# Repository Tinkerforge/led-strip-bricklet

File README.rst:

LED Strip Bricklet
==================

This repository contains the firmware source code and the hardware design
files. The documentation generator configs can be found at
https://github.com/Tinkerforge/generators

Repository Content
------------------

software/:
 * examples/: Examples for all supported languages
 * build/: Compiled files
 * src/: Source code of firmware
 * Makefile: Makefile to build project

hardware/:
 * Contains KiCad project files and additionally schematics as PDF

datasheets/:
 * Contains datasheets for sensors and complex ICs that are used

Hardware
--------

The hardware is designed with the open source EDA Suite KiCad
(http://www.kicad.org). Before you are able to open the files,
you have to install the Tinkerforge kicad-libraries
(https://github.com/Tinkerforge/kicad-libraries). You can either clone
them directly in hardware/ or clone them in a separate folder and
symlink them into hardware/
(ln -s kicad_path/kicad-libraries project_path/hardware). After that you
can open the .pro file in hardware/ with KiCad and from there view and
modify the schematics and the PCB layout.

Software
--------

If you want to do your own Brick/Bricklet firmware development we highly
recommend that you use our build environment setup script and read the
tutorial (https://www.tinkerforge.com/en/doc/Tutorials/Tutorial_Build_Environment/Tutorial.html).

To compile the C code we recommend you to install the newest GNU Arm Embedded
Toolchain (https://launchpad.net/gcc-arm-embedded/+download).
You also need to install bricklib (https://github.com/Tinkerforge/bricklib)
and brickletlib (https://github.com/Tinkerforge/brickletlib).

You can either clone it directly in software/src/ or clone it in a
separate folder and symlink it into software/src/
(ln -s bricklib_path/bricklib project_path/software/src/ and
ln -s brickletlib_path/brickletlib project_path/software/src/).
Finally make sure to have CMake installed
(http://www.cmake.org/cmake/resources/software.html).

After that you can build the firmware by invoking make in software/.
The firmware (.bin) can then be found in software/build/ and uploaded
with brickv (click button "Flashing" on start screen).

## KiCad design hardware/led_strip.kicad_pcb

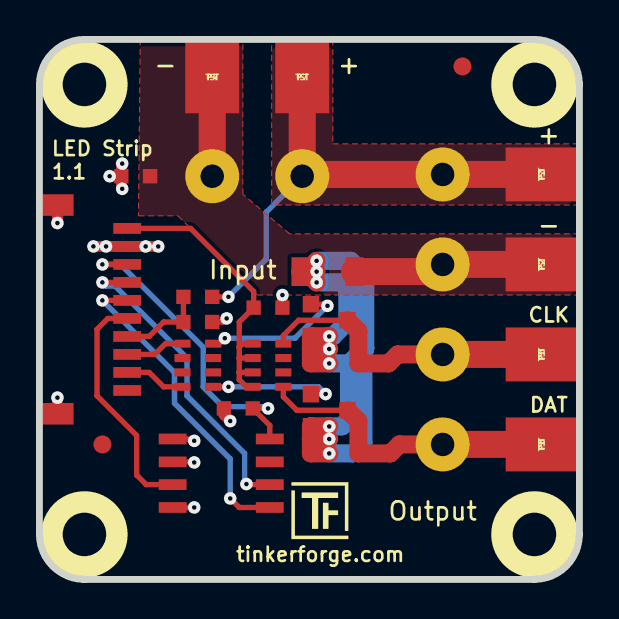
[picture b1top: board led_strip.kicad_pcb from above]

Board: 2 copper layers, 30.0 x 30.0 mm, 31 parts (0 on the bottom side), 16 nets.

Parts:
C1, C2: 100nF; C0603
D1, D2: ESD5V0D3B-TP; SOD-323
F1: FUSE; F1206
Fiducial_Mark: VAL**; Fiducial_Mark
Fiducial_Mark#2: VAL**; Fiducial_Mark
J1, J2, J3: AKL_5_2
L1: FB; C0603
P1: CON-SENSOR
P2, P3, P4, P5, P6, P7: TST; SOLDER_PAD2
Q1, Q2: 2N7002P; SOT23GDS
R1: 1k; R0603
R2: 10k; R0603
RP1: 470; 4X0603
RP2: 1k; 4X0603
U1: M24C64; SOIC8
U2, U3, U4, U5: DRILL; DRILL_NP
VAL: WEEE_7mm
VAL#2: CE_5mm

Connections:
+5V: C2.1, P1.1, RP2.5, RP2.6, RP2.7, RP2.8
AGND: F1.2, J1.1, J2.2, L1.2, P2.1, P4.1
GND: C1.2, C2.2, L1.1, P1.2, P1.EP, R1.1, U1.1, U1.2, U1.4
unnamed: D1.1, J3.1, P5.1, Q1.D, RP2.1
unnamed: D1.2, D2.2, F1.1, Q1.S, Q2.S
unnamed: D2.1, J3.2, P6.1, Q2.D, RP2.4
unnamed: J1.2, J2.1, P3.1, P7.1, R2.2
unnamed: P1.4, U1.6
unnamed: P1.5, U1.5
unnamed: P1.6, U1.3
unnamed: P1.7, R1.2, R2.1
unnamed: P1.8, RP1.8
unnamed: P1.9, RP1.5
unnamed: Q1.G, RP1.1
unnamed: Q2.G, RP1.4
VCC: C1.1, P1.3, U1.8

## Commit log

2013-09-17 Change optimization from 3 to 2
2013-09-17 Add support for multiple brick contexts
2013-09-20 c: Avoid unused parameter warning
2013-10-15 add hardware files
2013-10-17 add missing license file
2013-10-18 Fix name to fit naming standard
2013-10-29 Fix variable type in loop (we need uint16 instead of uint8)
2013-10-30 Add missing LED Strip examples for ruby and python
2013-10-30 Don't use data in case of error
2013-11-19 update schematic to correct resistor values
2013-11-19 update hardware files with new resistor values
2013-11-27 ruby: Fix whitespace
2013-12-02 Fix typo
2013-12-06 Add Get/SetClockFrequency function
2013-12-19 php: Cleanup example
2014-01-08 Fix typos
2014-01-10 Add Perl examples
2014-01-14 perl: Fix warning about unsharing the $led_strip variable
2014-02-07 Add Mathematica examples
2014-02-10 Perl Example Modified: LED Strip Bricklet callback
2014-02-10 perl: fixed namespace
2014-02-12 javascript: add examples
2014-02-18 javascript: examples fixed
2014-02-20 javascript: add html examples
2014-02-24 javascript: port 4280, startExample()
2014-02-28 javascript: Break long lines and cleanup whitespace
2014-03-05 Add LabVIEW examples
2014-03-06 labview: Add examples in LV2010 format
2014-03-31 matlab: add examples
2014-04-02 java: Unify constants style
2014-04-02 perl: Unify print style
2014-04-17 matlab: Adapt examples to new callback style
2014-04-17 matlab: Add parentheses to make pygments happy
2014-07-03 Add support for WS2811 and WS2812
2014-07-04 Make WS2811 and WS2812 protocol implementation more precise
2014-07-07 Update changelog
2014-07-10 Use timings based on measured values, not according to datasheet
2014-07-15 java: Replace System.console() usage with an Eclipse compatible pattern
2014-07-22 * Frame duration of 0 now means that no more frames shall be set * Set RGB values at least two times to make sure that they are really written * Fix possible overflow if Brick with two Bricklet conne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
2014-07-22 Add changelog for 2.0.5
2014-08-05 delphi: Remove unused variable
2014-12-02 Use ReadLine instead of ReadKey for C# example
2015-02-13 vbnet: Use ReadLine instead of ReadKey
    Because ReadKey doesn't work with a pipe as stdin on the RED Brick.
2015-03-02 windows: Stop cmake from searching for mingw32-make.exe
    Using MinGW Makefiles as generator makes cmake search for mingw32-make.exe
    which might not be installed because GnuWin32's make.exe is used instead.
2015-03-03 delphi: Fix type mismatch error in Delphi IDE
    Object Pascal doesn't allow static array definitions in function and
    procedure signatures. As workaround a external type definition has to
    be used.
    The Delphi IDE reports a type mismatch error if array [0..15] of byte
    and TArray0To15OfUInt8 are mixed. In contrast FPC allows to mix this.
2015-04-09 c: Whitespace
2015-07-08 new prototype of led strip bricklet
2015-07-25 Make JavaScript browser example textarea readonly
2015-07-27 Cleanup C/C++, C#, Java, Python and Ruby examples
2015-07-27 Simplify variable names in examples again
2015-07-28 Add missing final modifier in Java example and fix variable name in C/C++ example
2015-07-29 Reformat changelog
2015-08-07 Use full device class name in Python examples
2015-08-12 Fix minor warnings in C/C++ examples
2015-08-17 Cleanup Delphi examples
2015-08-18 Cleanup VB.NET examples
2015-08-19 Cleanup Perl examples
2015-09-09 Duplicate cmake call to fix bug during cmake creation
2015-09-25 drc run
2015-10-05 Generator based example cleanup
2015-11-12 matlab: Fix callback handling for R2014a
    http://undocumentedmatlab.com/blog/matlab-callbacks-for-java-events-in-r2014a
2015-11-25 Include date and commit into changelog
2016-05-18 c: Add missing device destroy call
2016-07-01 Make the change UID comment more explicit
2016-07-19 Add RGBW support for WS2812 style timing
2016-07-27 Add support for new chip type: LPD8806
2016-07-28 Add support for new chip type: APA102 (Adafruit DotStar)
2016-08-01 Add brightness control for APA102
    Does not work with Master Brick FW 2.4.0
2016-08-01 Use option functions to make code more readable
2016-08-01 Use Os
2016-08-01 Add datasheets for all supported chip types
2016-08-02 little cleanup
2016-08-11 Add channel mapping and code optimization
2016-08-11 Remove debug code
2016-09-01 Reduce code size by refactoring common and unused code
    Also free up a byte in the BrickContext.
2016-09-01 Cleanup bb_write functions
2016-09-01 Whitespace
2016-09-01 Add defines for channel mappings
2016-09-01 Add SK6812 datasheets
2016-09-02 Apply channel mapping in RGB(W) getter
    Restructure buffer handling to reduce code size.
    Alos fix frame_max_length calculation in RGBW mode.
2016-09-02 Add missing APA102 endframe
2016-09-02 Minor style cleanup
2016-09-02 Fix default channel mapping
2016-09-02 Fix loop in RGB(W) getters
2016-09-02 Send correct number of zero bytes for LPD8806
2016-09-06 Make channel mapping constants contain the actual mapping table
    Also store channels unmapped and map them before sending to the LEDs.
    This allows to change the mapping for already set RGB(W) values.
2016-09-06 Add option to disable frame-rendered callback
2016-09-06 Add missing setter return
2016-09-07 Fix green flash after reset
    MOSFET inverts logic, initial pin state needs to be high to ensure low
    output until first frame.
2016-09-07 Use local bc variable
2016-09-08 Add changelog commit after the fact
2017-04-13 csharp: Adapt example
2017-06-02 octave: Use javaObject instead of deprecated java_new
2017-07-31 Fix broken symbols
2017-07-31 New schematic version
2017-07-31 Add 3d information (final)
2017-07-31 Add 3d model (*.step & *.FCStd)
2017-11-30 Update examples from generator
2017-12-07 mathematica: Also generate .nb files
2018-02-19 javascript: Close div tag correctly
2018-02-20 Cleanup KiCad libraries config
    Ensure LibDir=kicad-libraries and LibName1=tinkerforge.
    Remove special library.
2018-03-28 specify fuse
2018-05-11 Rename files
2018-05-24 perl: Use strict in examples
2018-07-11 Add Makefile with docker support
2018-07-11 Update directory structure and build instructions
2018-07-11 Remove obsolete generate_makefile scripts
2018-11-06 Add rust examples
2018-11-07 rust: Accept host names for ip connection, fix naming inconsistencies
2018-11-07 rust: Rename callback receivers.
2018-12-14 Add go examples.
2018-12-18 go: Change import path.
2018-12-18 go: Change import path again.
2018-12-20 rust: Reformat examples.
2019-01-24 mqtt: Add examples.
2019-01-24 mqtt: Remove executable bit in example permissions.
2019-01-24 go: Minor example fixes.
2019-03-28 mqtt: Fix whitespace.
2019-03-28 Replace example with auto-generated one.
2019-08-22 c: Adapt to bindings changes
2020-01-13 examples: Use python3 input instead of python2 raw_input.
2020-01-13 examples: mqtt: Remove trailing whitespace.
2020-01-14 Revert "examples: mqtt: Remove trailing whitespace."
    This reverts commit 828755622c517519aeb3ec8f6998cfd395dc9233.
2020-01-14 examples: Use python3 input by default.
2020-03-16 rust: Update to new skeleton
2020-03-18 delphi: Avoid keywords
2020-04-07 examples: rust: Always block when calling bindings functions.
2021-10-25 Update KiCad link
    https://www.kicad.org/blog/2021/10/Avoid-links-to-former-kicad-domain/
2022-07-06 Add license files.

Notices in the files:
hardware/led_strip.kicad_pcb:
Licensed under CERN OHL v.1.1
Copyright (©) 2015, B.Nordmeyer
Copyright Tinkerforge GmbH 2013.
This documentation describes Open Hardware and is licensed under the
CERN OHL v. 1.1.
